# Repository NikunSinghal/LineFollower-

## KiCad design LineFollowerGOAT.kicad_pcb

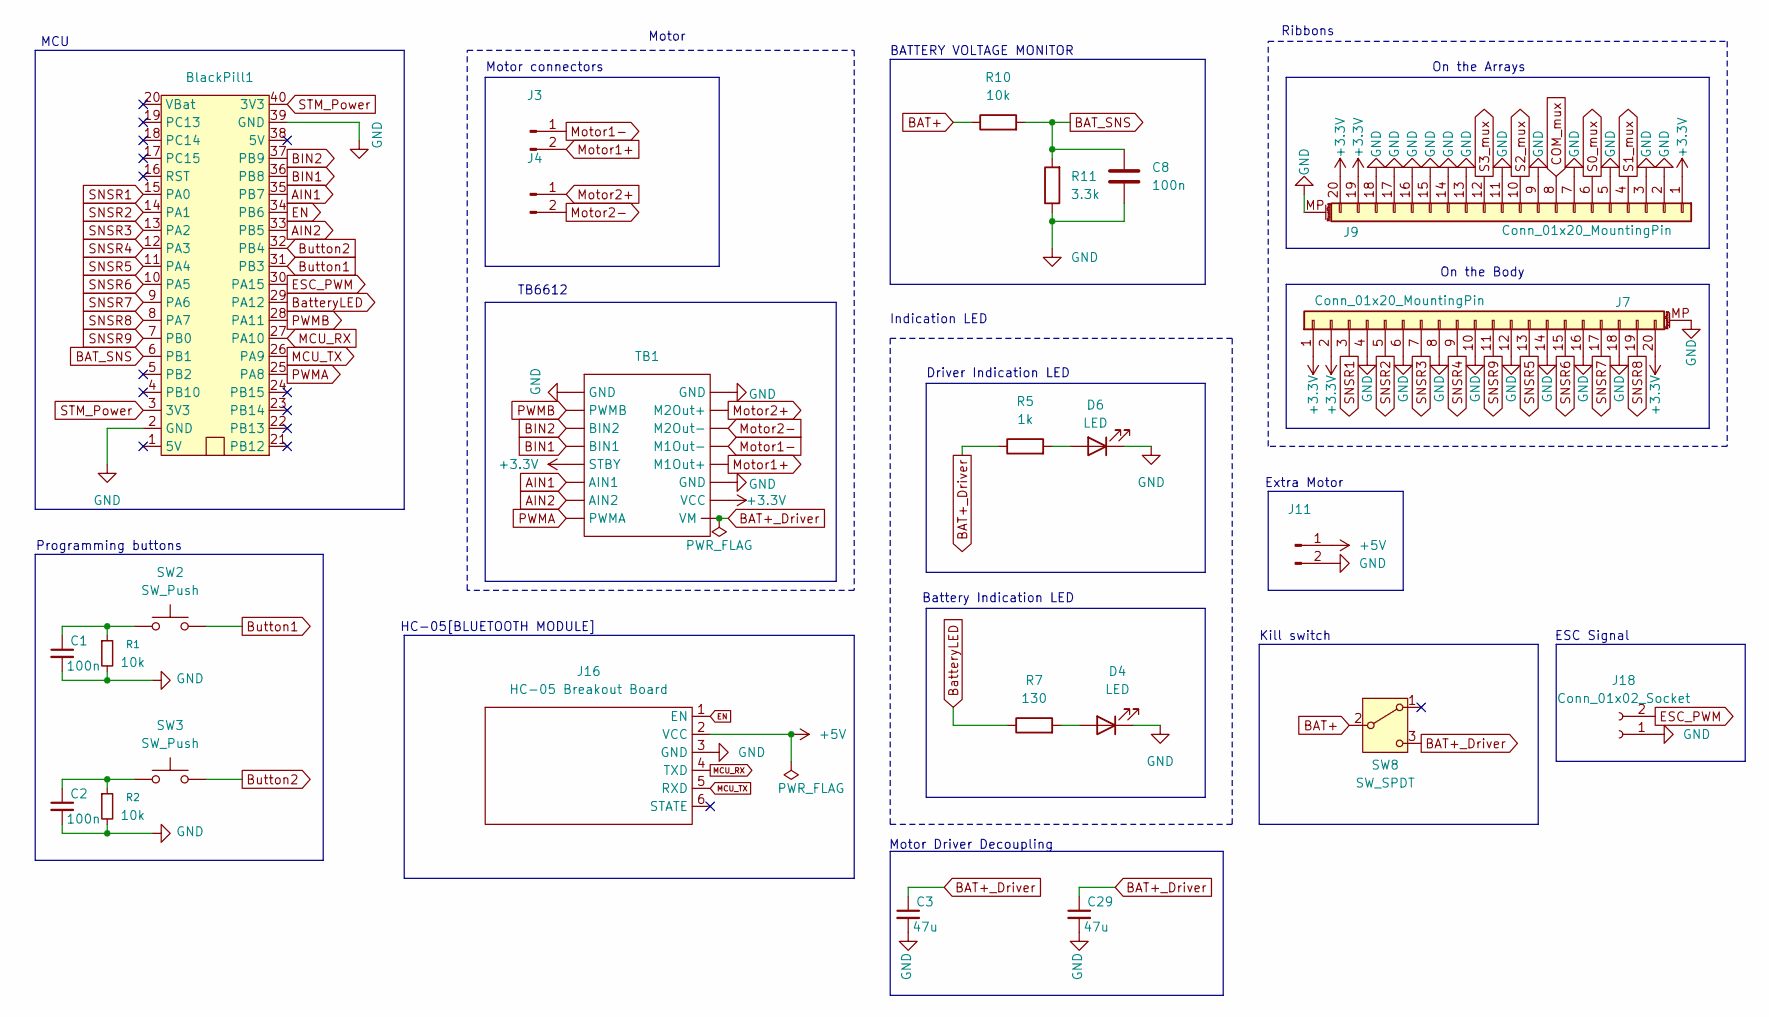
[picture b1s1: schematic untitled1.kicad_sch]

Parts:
BlackPill1: STM32F411_BP; blackpill_fp
C1, C2, C8: 100n; C_0603_1608Metric_Pad1.08x0.95mm_HandSolder
C3, C29: 47u; C_0603_1608Metric_Pad1.08x0.95mm_HandSolder
D4, D6: LED; LED_0603_1608Metric_Pad1.05x0.95mm_HandSolder
J3, J4: Conn_01x02_Pin; JST_PH_B2B-PH-K_1x02_P2.00mm_Vertical
J7, J9: Conn_01x20_MountingPin; Amphenol_F32Q-1A7x1-11020_1x20-1MP_P0.5mm_Horizontal
J11: Conn_01x02_Pin; PinHeader_1x02_P2.00mm_Vertical
J16: HC-05 Breakout Board; PinSocket_1x06_P2.54mm_Vertical
J18: Conn_01x02_Socket; JST_PH_B2B-PH-K_1x02_P2.00mm_Vertical
R1, R2, R10: 10k; R_0603_1608Metric_Pad0.98x0.95mm_HandSolder
R5: 1k; R_0603_1608Metric_Pad0.98x0.95mm_HandSolder
R7: 130; R_0603_1608Metric_Pad0.98x0.95mm_HandSolder
R11: 3.3k; R_0603_1608Metric_Pad0.98x0.95mm_HandSolder
SW2, SW3: SW_Push; Push button-fp
SW8: SW_SPDT; SW_Slide_SPDT_Angled_CK_OS102011MA1Q
TB1: TB6612 module

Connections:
+3.3V: J7.1, J7.2, J7.20, J9.1, J9.19, J9.20, TB1.5 (STBY), TB1.15 (VCC); also elsewhere on the board
+5V: J11.1, J16.2 (VCC); also elsewhere on the board
AIN1: BlackPill1.35 (PB7), TB1.6 (AIN1)
AIN2: BlackPill1.33 (PB5), TB1.7 (AIN2)
BAT+: R10.1, SW8.2 (B); also elsewhere on the board
BAT+_Driver: C3.1, C29.1, R5.1, SW8.3 (C), TB1.16 (VM)
BAT_SNS: BlackPill1.6 (PB1), C8.1, R10.2, R11.2
BIN1: BlackPill1.36 (PB8), TB1.4 (BIN1)
BIN2: BlackPill1.37 (PB9), TB1.3 (BIN2)
BatteryLED: BlackPill1.29 (PA12), R7.1
Button1: BlackPill1.31 (PB3), SW2.2
Button2: BlackPill1.32 (PB4), SW3.2
COM_mux: J9.8; also elsewhere on the board
EN: BlackPill1.34 (PB6), J16.1 (EN)
ESC_PWM: BlackPill1.30 (PA15), J18.2
GND: BlackPill1.2 (GND), BlackPill1.39 (GND), C1.2, C2.2, C3.2, C8.2, C29.2, D4.1 (K), D6.1 (K), J7.4, J7.6, J7.8, J7.10, J7.12, J7.14, J7.16, J7.18, J7.MP (MountPin), J9.2, J9.3, J9.5, J9.7, J9.9, J9.11, J9.13, J9.14, J9.15, J9.16, J9.17, J9.18, J9.MP (MountPin), J11.2, J16.3 (GND), J18.1, R1.2, R2.2, R11.1, TB1.1 (GND), TB1.9 (GND), TB1.14 (GND); also elsewhere on the board
MCU_RX: BlackPill1.27 (PA10), J16.4 (TXD)
MCU_TX: BlackPill1.26 (PA9), J16.5 (RXD)
Motor1+: J3.2, TB1.13 (M1Out+)
Motor1-: J3.1, TB1.12 (M1Out-)
Motor2+: J4.1, TB1.10 (M2Out+)
Motor2-: J4.2, TB1.11 (M2Out-)
unnamed: C1.1, R1.1, SW2.1
unnamed: C2.1, R2.1, SW3.1
unnamed: D4.2 (A), R7.2
unnamed: D6.2 (A), R5.2
PWMA: BlackPill1.25 (PA8), TB1.8 (PWMA)
PWMB: BlackPill1.28 (PA11), TB1.2 (PWMB)
S0_mux: J9.6; also elsewhere on the board
S1_mux: J9.4; also elsewhere on the board
S2_mux: J9.10; also elsewhere on the board
S3_mux: J9.12; also elsewhere on the board
SNSR1: BlackPill1.15 (PA0), J7.3
SNSR2: BlackPill1.14 (PA1), J7.5
SNSR3: BlackPill1.13 (PA2), J7.7
SNSR4: BlackPill1.12 (PA3), J7.9
SNSR5: BlackPill1.11 (PA4), J7.13
SNSR6: BlackPill1.10 (PA5), J7.15
SNSR7: BlackPill1.9 (PA6), J7.17
SNSR8: BlackPill1.8 (PA7), J7.19
SNSR9: BlackPill1.7 (PB0), J7.11
STM_Power: BlackPill1.3 (3V3), BlackPill1.40 (3V3); also elsewhere on the board

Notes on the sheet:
On the Body
Motor Driver Decoupling
Driver Indication LED
TB6612
Battery Indication LED
HC-05[BLUETOOTH MODULE]
Motor
BATTERY VOLTAGE MONITOR
ESC Signal
Motor connectors
MCU
Indication LED
Ribbons
On the Arrays
Kill switch
Programming buttons
Extra Motor

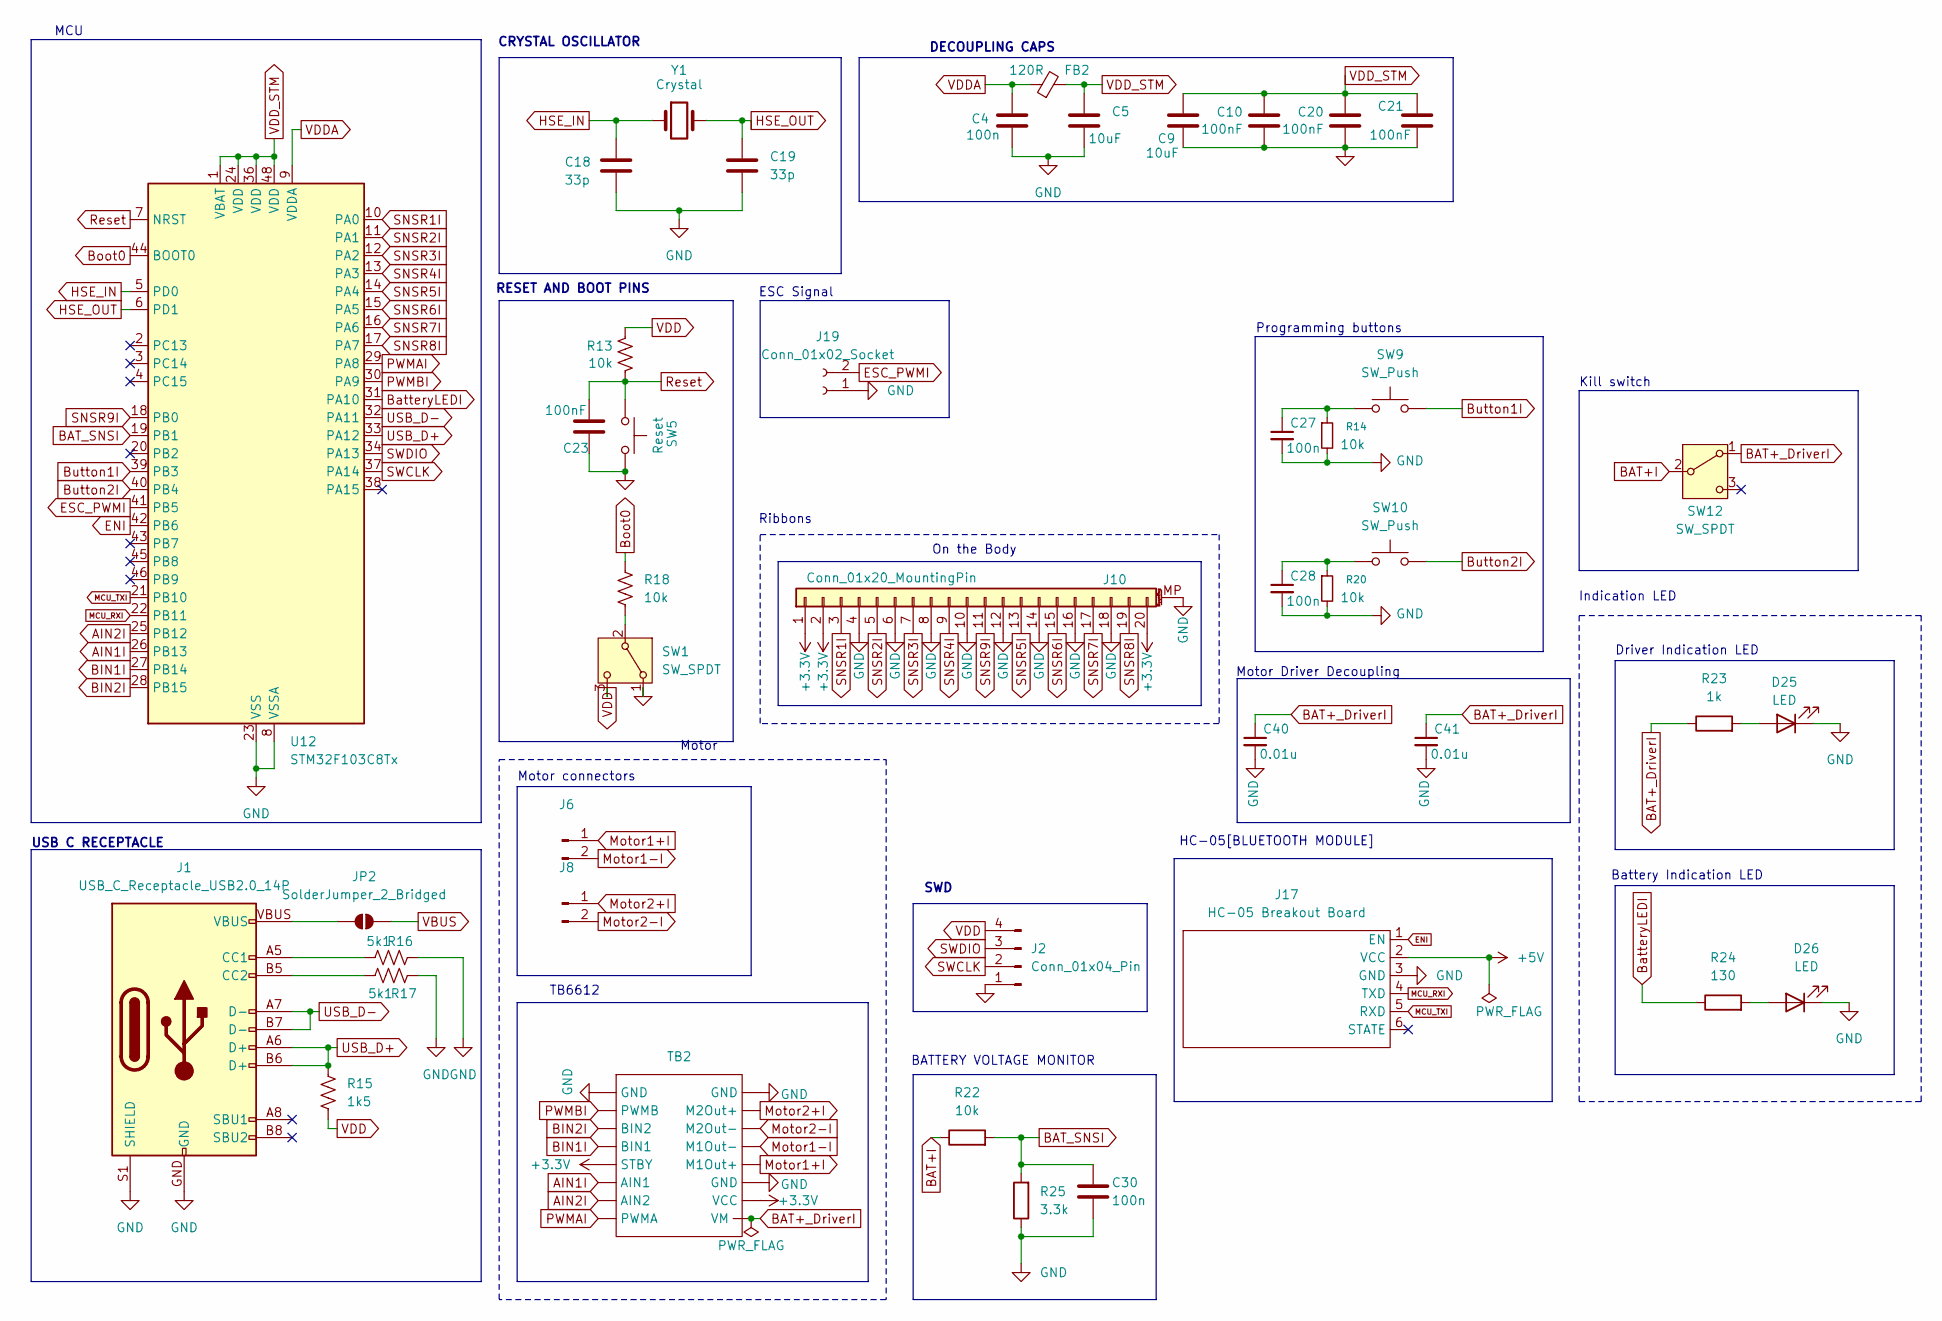
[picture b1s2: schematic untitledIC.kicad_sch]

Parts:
C4, C27, C28, C30: 100n; C_0603_1608Metric_Pad1.08x0.95mm_HandSolder
C5, C9: 10uF; C_0603_1608Metric_Pad1.08x0.95mm_HandSolder
C10, C20, C21, C23: 100nF; C_0603_1608Metric_Pad1.08x0.95mm_HandSolder
C18, C19: 33p; C_0603_1608Metric_Pad1.08x0.95mm_HandSolder
C40, C41: 0.01u; C_0603_1608Metric_Pad1.08x0.95mm_HandSolder
D25, D26: LED; LED_0603_1608Metric_Pad1.05x0.95mm_HandSolder
FB2: 120R; L_0603_1608Metric_Pad1.05x0.95mm_HandSolder
J1: USB_C_Receptacle_USB2.0_14P; USB-C-16P
J2: Conn_01x04_Pin; PinHeader_1x04_P2.00mm_Vertical
J6, J8: Conn_01x02_Pin; JST_PH_B2B-PH-K_1x02_P2.00mm_Vertical
J10: Conn_01x20_MountingPin; Amphenol_F32Q-1A7x1-11020_1x20-1MP_P0.5mm_Horizontal
J17: HC-05 Breakout Board; PinSocket_1x06_P2.54mm_Vertical
J19: Conn_01x02_Socket; JST_PH_B2B-PH-K_1x02_P2.00mm_Vertical
JP2: SolderJumper_2_Bridged; SolderJumper-2_P1.3mm_Open_RoundedPad1.0x1.5mm
R13, R14, R18, R20, R22: 10k; R_0603_1608Metric_Pad0.98x0.95mm_HandSolder
R15: 1k5; R_0603_1608Metric_Pad0.98x0.95mm_HandSolder
R16, R17: 5k1; R_0603_1608Metric_Pad0.98x0.95mm_HandSolder
R23: 1k; R_0603_1608Metric_Pad0.98x0.95mm_HandSolder
R24: 130; R_0603_1608Metric_Pad0.98x0.95mm_HandSolder
R25: 3.3k; R_0603_1608Metric_Pad0.98x0.95mm_HandSolder
SW1: SW_SPDT; PinHeader_1x03_P2.00mm_Vertical
SW5: Reset; Push button-fp
SW9, SW10: SW_Push; Push button-fp
SW12: SW_SPDT; SW_Slide_SPDT_Angled_CK_OS102011MA1Q
TB2: TB6612 module
U12: STM32F103C8Tx; LQFP-48_7x7mm_P0.5mm
Y1: Crystal; Crystal_SMD_HC49-SD

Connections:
+3.3V: J10.1, J10.2, J10.20, TB2.5 (STBY), TB2.15 (VCC); also elsewhere on the board
+5V: J17.2 (VCC); also elsewhere on the board
AIN1I: TB2.6 (AIN1), U12.26 (PB13)
AIN2I: TB2.7 (AIN2), U12.25 (PB12)
BAT+I: R22.1, SW12.2 (B); also elsewhere on the board
BAT+_DriverI: C40.1, C41.1, R23.1, SW12.1 (A), TB2.16 (VM)
BAT_SNSI: C30.1, R22.2, R25.2, U12.19 (PB1)
BIN1I: TB2.4 (BIN1), U12.27 (PB14)
BIN2I: TB2.3 (BIN2), U12.28 (PB15)
BatteryLEDI: R24.1, U12.31 (PA10)
Boot0: R18.2, U12.44 (BOOT0)
Button1I: SW9.2, U12.39 (PB3)
Button2I: SW10.2, U12.40 (PB4)
ENI: J17.1 (EN), U12.42 (PB6)
ESC_PWMI: J19.2, U12.41 (PB5)
GND: C4.2, C5.2, C9.2, C10.2, C18.2, C19.2, C20.2, C21.2, C23.1, C27.2, C28.2, C30.2, C40.2, C41.2, D25.1 (K), D26.1 (K), J1.A12 (GND), J1.B1 (GND), J1.B12 (GND), J1.GND, J1.S1 (SHIELD), J2.1, J10.4, J10.6, J10.8, J10.10, J10.12, J10.14, J10.16, J10.18, J10.MP (MountPin), J17.3 (GND), J19.1, R14.2, R16.2, R17.2, R20.2, R25.1, SW1.1 (A), SW5.2, TB2.1 (GND), TB2.9 (GND), TB2.14 (GND), U12.8 (VSSA), U12.23 (VSS), U12.35 (VSS), U12.47 (VSS); also elsewhere on the board
HSE_IN: C18.1, U12.5 (PD0), Y1.1
HSE_OUT: C19.1, U12.6 (PD1), Y1.2
MCU_RXI: J17.4 (TXD), U12.22 (PB11)
MCU_TXI: J17.5 (RXD), U12.21 (PB10)
Motor1+I: J6.1, TB2.13 (M1Out+)
Motor1-I: J6.2, TB2.12 (M1Out-)
Motor2+I: J8.1, TB2.10 (M2Out+)
Motor2-I: J8.2, TB2.11 (M2Out-)
unnamed: C27.1, R14.1, SW9.1
unnamed: C28.1, R20.1, SW10.1
unnamed: D25.2 (A), R23.2
unnamed: D26.2 (A), R24.2
unnamed: J1.A5 (CC1), R16.1
unnamed: J1.B5 (CC2), R17.1
unnamed: J1.A9 (VBUS), J1.B4 (VBUS), J1.B9 (VBUS), J1.VBUS, JP2.1 (A)
unnamed: R18.1, SW1.2 (B)
PWMAI: TB2.8 (PWMA), U12.29 (PA8)
PWMBI: TB2.2 (PWMB), U12.30 (PA9)
Reset: C23.2, R13.1, SW5.1, U12.7 (NRST)
SNSR1I: J10.3, U12.10 (PA0)
SNSR2I: J10.5, U12.11 (PA1)
SNSR3I: J10.7, U12.12 (PA2)
SNSR4I: J10.9, U12.13 (PA3)
SNSR5I: J10.13, U12.14 (PA4)
SNSR6I: J10.15, U12.15 (PA5)
SNSR7I: J10.17, U12.16 (PA6)
SNSR8I: J10.19, U12.17 (PA7)
SNSR9I: J10.11, U12.18 (PB0)
SWCLK: J2.2, U12.37 (PA14)
SWDIO: J2.3, U12.34 (PA13)
USB_D+: J1.A6 (D+), J1.B6 (D+), R15.1, U12.33 (PA12)
USB_D-: J1.A7 (D-), J1.B7 (D-), U12.32 (PA11)
VBUS: JP2.2 (B); also elsewhere on the board
VDD: J2.4, R13.2, R15.2, SW1.3 (C); also elsewhere on the board
VDDA: C4.1, FB2.1, U12.9 (VDDA)
VDD_STM: C5.1, C9.1, C10.1, C20.1, C21.1, FB2.2, U12.1 (VBAT), U12.24 (VDD), U12.36 (VDD), U12.48 (VDD); also elsewhere on the board

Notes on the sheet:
Programming buttons
Indication LED
CRYSTAL OSCILLATOR
On the Body
Motor Driver Decoupling
MCU
BATTERY VOLTAGE MONITOR
DECOUPLING CAPS
Battery Indication LED
Kill switch
ESC Signal
USB C RECEPTACLE
HC-05[BLUETOOTH MODULE]
Motor
Driver Indication LED
SWD
RESET AND BOOT PINS
Motor connectors
TB6612
Ribbons

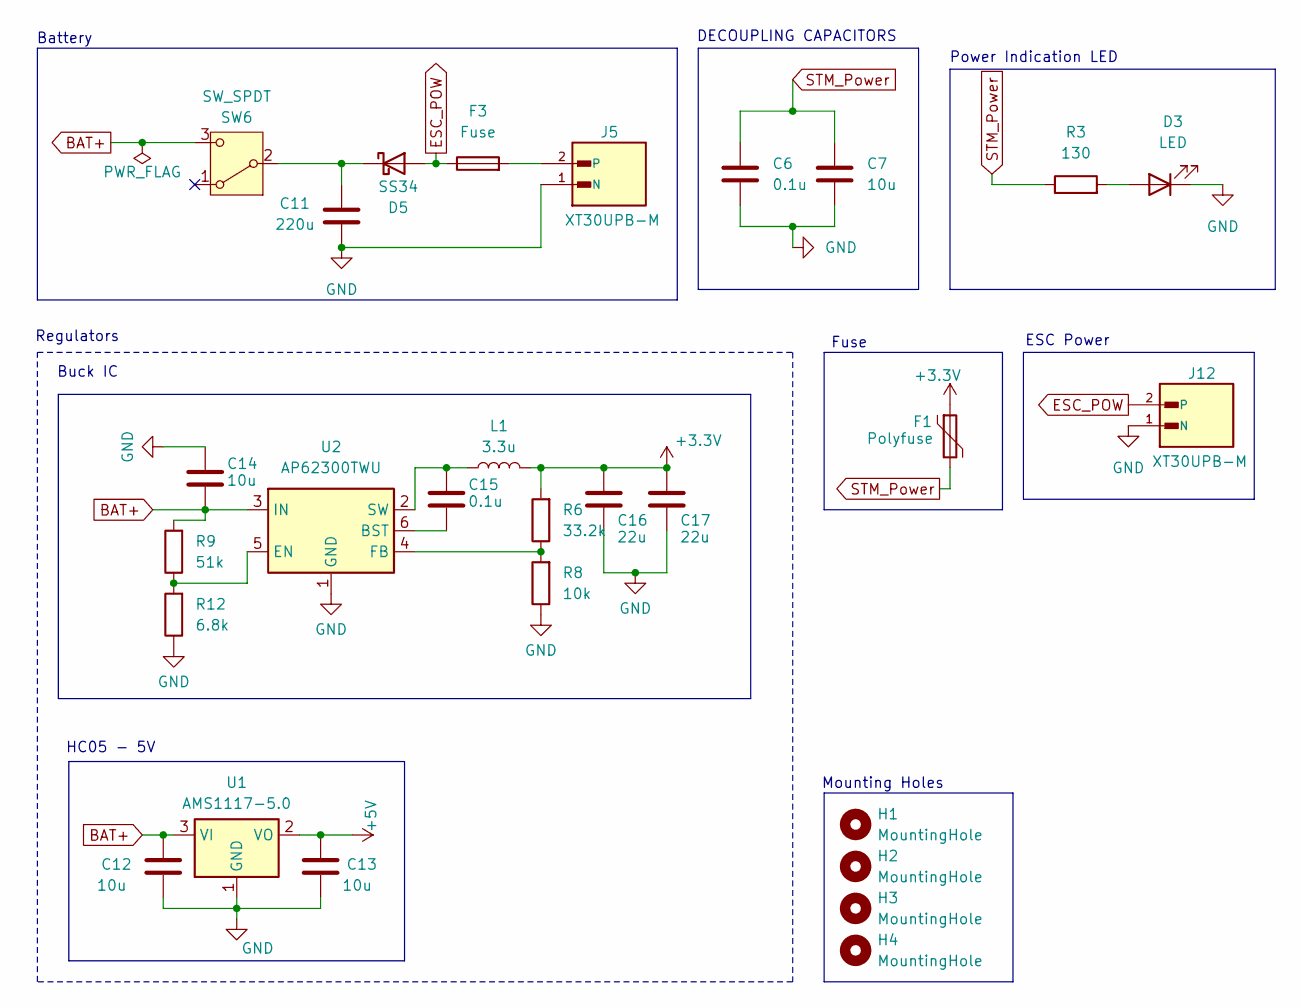
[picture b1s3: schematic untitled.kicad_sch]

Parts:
C6, C15: 0.1u; C_0603_1608Metric_Pad1.08x0.95mm_HandSolder
C7, C12, C13, C14: 10u; C_0603_1608Metric_Pad1.08x0.95mm_HandSolder
C11: 220u; CP_Radial_D6.3mm_P2.50mm
C16, C17: 22u; C_0603_1608Metric_Pad1.08x0.95mm_HandSolder
D3: LED; LED_0603_1608Metric_Pad1.05x0.95mm_HandSolder
D5: SS34; D_SMA_Handsoldering
F1: Polyfuse; Fuse_0805_2012Metric_Pad1.15x1.40mm_HandSolder
F3: Fuse; C_1808_4520Metric
H1, H2, H3, H4: MountingHole; MountingHole_3mm
J5, J12: XT30UPB-M; AMASS_XT30UPB-M_1x02_P5.0mm_Vertical
L1: 3.3u; L_Sunlord_SWPA5040S
R3: 130; R_0603_1608Metric_Pad0.98x0.95mm_HandSolder
R6: 33.2k; R_0603_1608Metric_Pad0.98x0.95mm_HandSolder
R8: 10k; R_0603_1608Metric_Pad0.98x0.95mm_HandSolder
R9: 51k; R_0603_1608Metric_Pad0.98x0.95mm_HandSolder
R12: 6.8k; R_0603_1608Metric_Pad0.98x0.95mm_HandSolder
SW6: SW_SPDT; SW_Slide_SPDT_Angled_CK_OS102011MA1Q
U1: AMS1117-5.0; SOT-223-3_TabPin2
U2: AP62300TWU; TSOT-23-6

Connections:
+3.3V: C16.1, C17.1, F1.1, L1.2, R6.2; also elsewhere on the board
+5V: C13.1, U1.2 (VO); also elsewhere on the board
BAT+: C12.1, C14.2, R9.2, SW6.3 (C), U1.3 (VI), U2.3 (IN); also elsewhere on the board
ESC_POW: D5.2 (A), F3.1, J12.2
GND: C6.2, C7.2, C11.2, C12.2, C13.2, C14.1, C16.2, C17.2, D3.1 (K), J5.1 (N), J12.1 (N), R8.1, R12.1, U1.1 (GND), U2.1 (GND); also elsewhere on the board
unnamed: D3.2 (A), R3.2
unnamed: C11.1, D5.1 (K), SW6.2 (B)
unnamed: F3.2, J5.2
unnamed: C15.2, U2.6 (BST)
unnamed: R9.1, R12.2, U2.5 (EN)
unnamed: R6.1, R8.2, U2.4 (FB)
unnamed: C15.1, L1.1, U2.2 (SW)
STM_Power: C6.1, C7.1, F1.2, R3.1; also elsewhere on the board

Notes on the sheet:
Regulators
DECOUPLING CAPACITORS
Power Indication LED
ESC Power
Fuse
Battery
Buck IC
Mounting Holes
HC05 - 5V

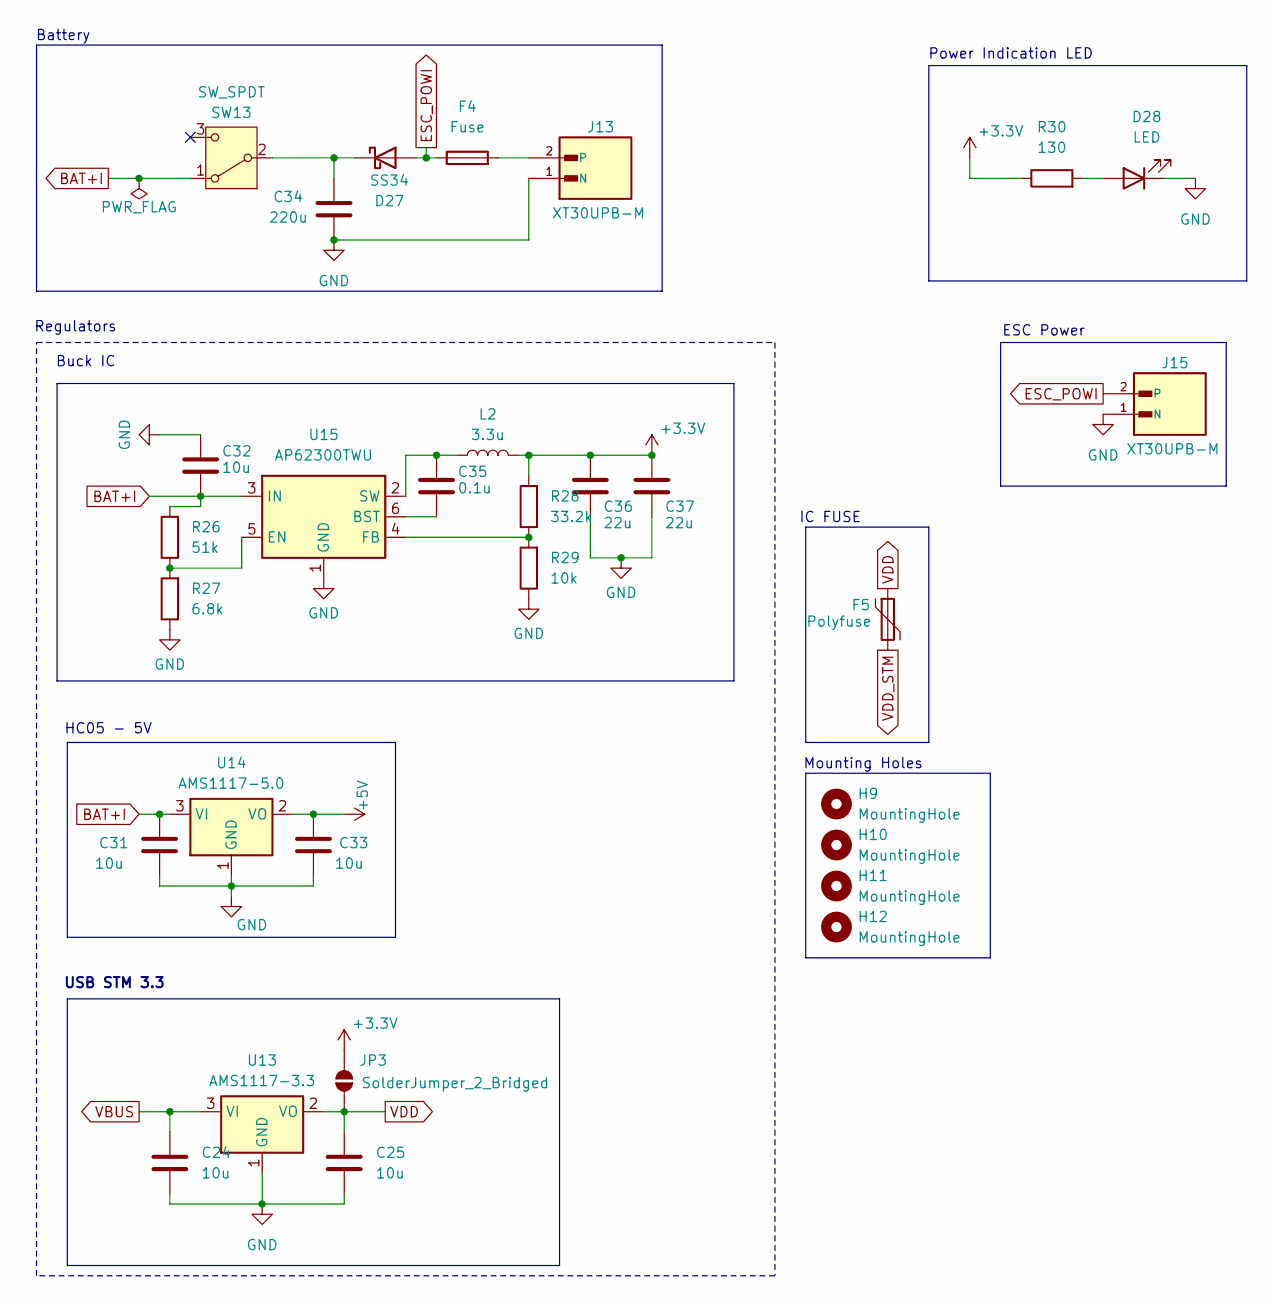
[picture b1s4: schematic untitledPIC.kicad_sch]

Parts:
C24, C25, C31, C32, C33: 10u; C_0603_1608Metric_Pad1.08x0.95mm_HandSolder
C34: 220u; CP_Radial_D6.3mm_P2.50mm
C35: 0.1u; C_0603_1608Metric_Pad1.08x0.95mm_HandSolder
C36, C37: 22u; C_0603_1608Metric_Pad1.08x0.95mm_HandSolder
D27: SS34; D_SMA_Handsoldering
D28: LED; LED_0603_1608Metric_Pad1.05x0.95mm_HandSolder
F4: Fuse; C_1808_4520Metric
F5: Polyfuse; Fuse_0805_2012Metric_Pad1.15x1.40mm_HandSolder
H9, H10, H11, H12: MountingHole; MountingHole_3mm
J13, J15: XT30UPB-M; AMASS_XT30UPB-M_1x02_P5.0mm_Vertical
JP3: SolderJumper_2_Bridged; SolderJumper-2_P1.3mm_Open_RoundedPad1.0x1.5mm
L2: 3.3u; L_Sunlord_SWPA5040S
R26: 51k; R_0603_1608Metric_Pad0.98x0.95mm_HandSolder
R27: 6.8k; R_0603_1608Metric_Pad0.98x0.95mm_HandSolder
R28: 33.2k; R_0603_1608Metric_Pad0.98x0.95mm_HandSolder
R29: 10k; R_0603_1608Metric_Pad0.98x0.95mm_HandSolder
R30: 130; R_0603_1608Metric_Pad0.98x0.95mm_HandSolder
SW13: SW_SPDT; SW_Slide_SPDT_Angled_CK_OS102011MA1Q
U13: AMS1117-3.3; SOT-223-3_TabPin2
U14: AMS1117-5.0; SOT-223-3_TabPin2
U15: AP62300TWU; TSOT-23-6

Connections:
+3.3V: C36.1, C37.1, JP3.2 (B), L2.2, R28.2, R30.1; also elsewhere on the board
+5V: C33.1, U14.2 (VO); also elsewhere on the board
BAT+I: C31.1, C32.2, R26.2, SW13.1 (A), U14.3 (VI), U15.3 (IN); also elsewhere on the board
ESC_POWI: D27.2 (A), F4.1, J15.2
GND: C24.2, C25.2, C31.2, C32.1, C33.2, C34.2, C36.2, C37.2, D28.1 (K), J13.1 (N), J15.1 (N), R27.1, R29.1, U13.1 (GND), U14.1 (GND), U15.1 (GND); also elsewhere on the board
unnamed: C34.1, D27.1 (K), SW13.2 (B)
unnamed: D28.2 (A), R30.2
unnamed: F4.2, J13.2
unnamed: C35.2, U15.6 (BST)
unnamed: R26.1, R27.2, U15.5 (EN)
unnamed: R28.1, R29.2, U15.4 (FB)
unnamed: C35.1, L2.1, U15.2 (SW)
VBUS: C24.1, U13.3 (VI); also elsewhere on the board
VDD: C25.1, F5.1, JP3.1 (A), U13.2 (VO); also elsewhere on the board
VDD_STM: F5.2; also elsewhere on the board

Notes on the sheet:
USB STM 3.3
Battery
ESC Power
Power Indication LED
HC05 - 5V
Buck IC
Mounting Holes
IC FUSE
Regulators

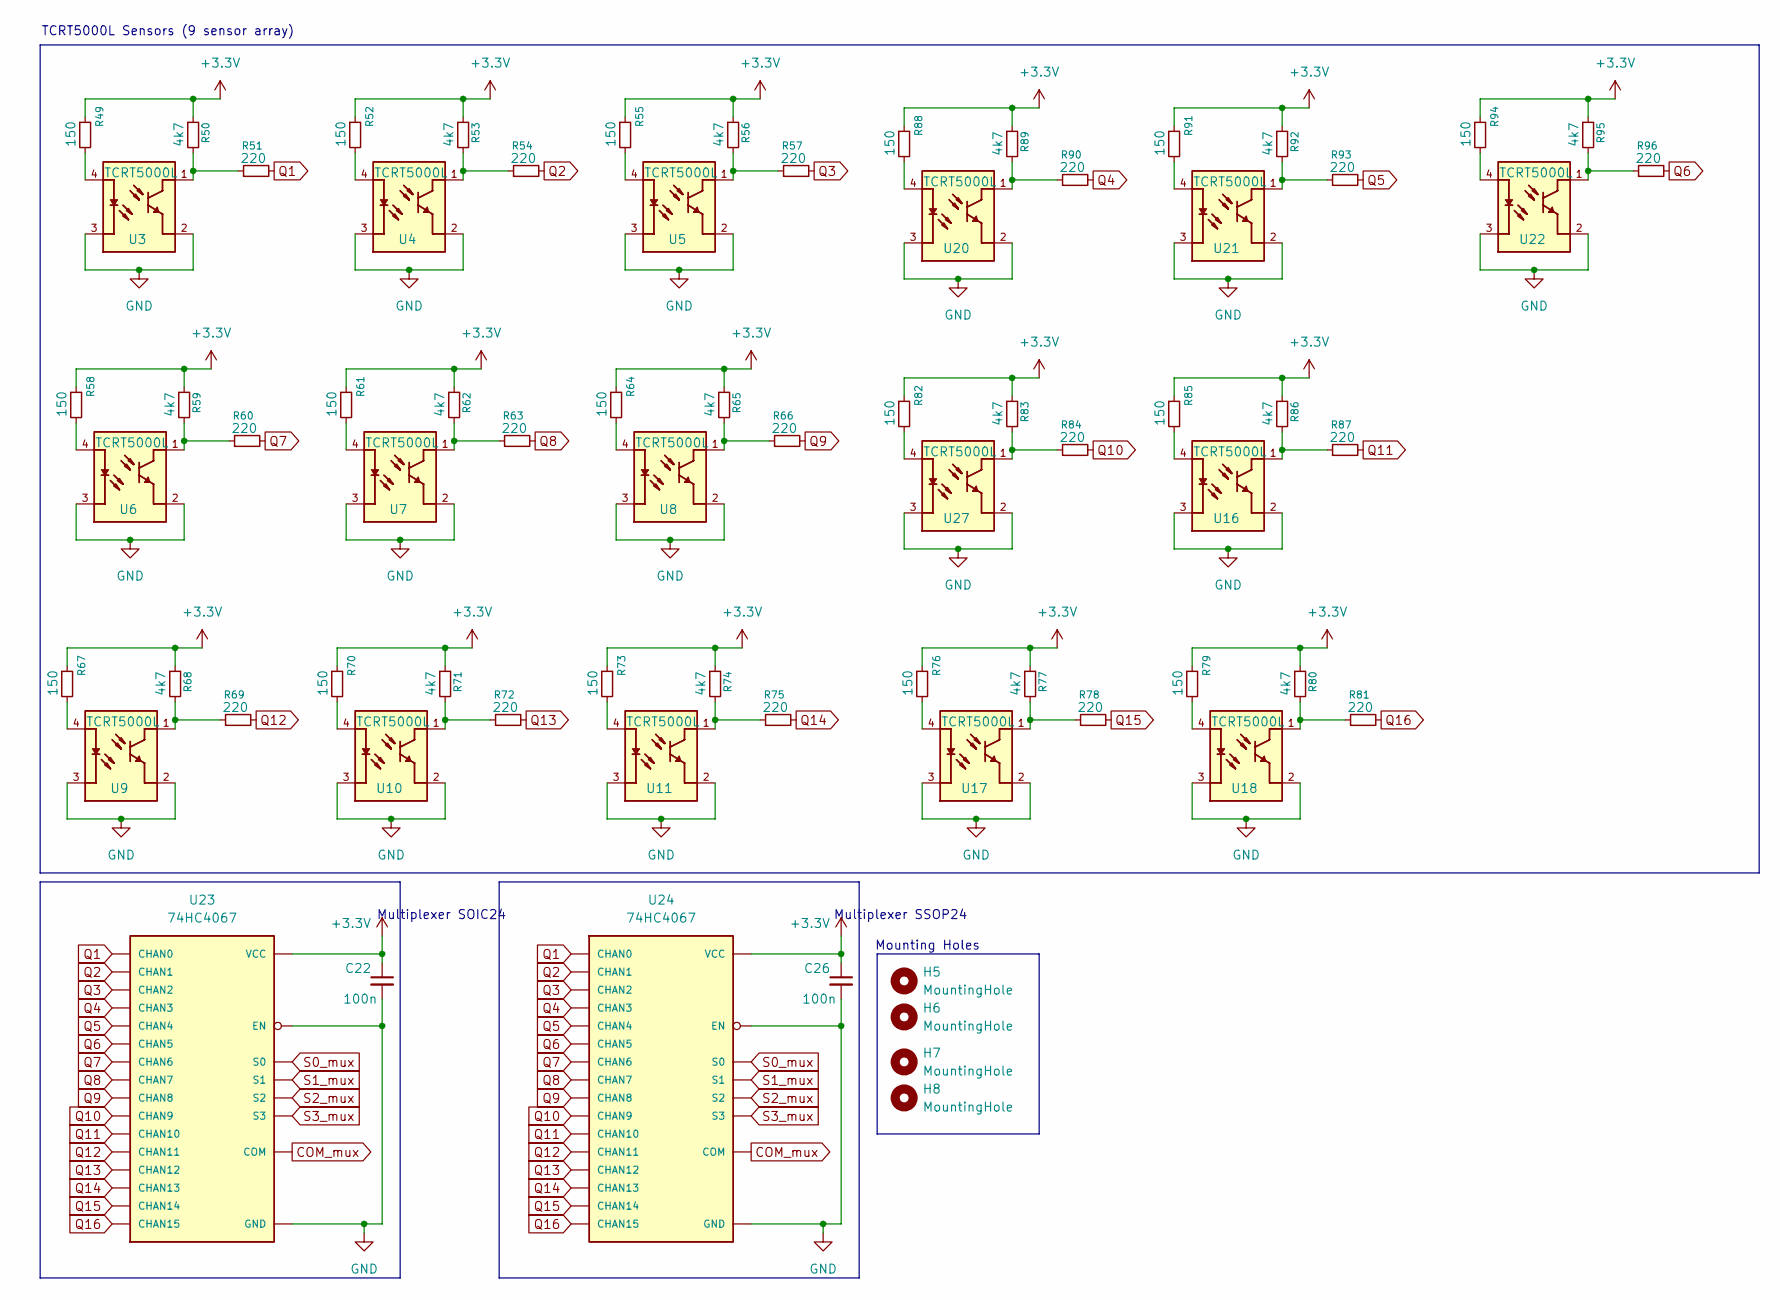
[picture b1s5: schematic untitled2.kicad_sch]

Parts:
C22, C26: 100n; C_0603_1608Metric_Pad1.08x0.95mm_HandSolder
H5, H6, H7, H8: MountingHole; MountingHole_3mm
R49, R52, R55, R58, R61, R64, R67, R70, R73, R76, R79, R82, R85, R88, R91, R94: 150; R_0603_1608Metric_Pad0.98x0.95mm_HandSolder
R50, R53, R56, R59, R62, R65, R68, R71, R74, R77, R80, R83, R86, R89, R92, R95: 4k7; R_0603_1608Metric_Pad0.98x0.95mm_HandSolder
R51, R54, R57, R60, R63, R66, R69, R72, R75, R78, R81, R84, R87, R90, R93, R96: 220; R_0603_1608Metric_Pad0.98x0.95mm_HandSolder
U3, U4, U5, U6, U7, U8, U9, U10, U11, U16, U17, U18, U20, U21, U22, U27: TCRT5000L; XDCR_TCRT5000L
U23: 74HC4067; SOIC-24W_7.5x15.4mm_P1.27mm
U24: 74HC4067; TSSOP-24_4.4x7.8mm_P0.65mm

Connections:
+3.3V: C22.1, C26.1, R49.1, R50.1, R52.1, R53.1, R55.1, R56.1, R58.1, R59.1, R61.1, R62.1, R64.1, R65.1, R67.1, R68.1, R70.1, R71.1, R73.1, R74.1, R76.1, R77.1, R79.1, R80.1, R82.1, R83.1, R85.1, R86.1, R88.1, R89.1, R91.1, R92.1, R94.1, R95.1, U23.24 (VCC), U24.24 (VCC); also elsewhere on the board
COM_mux: U23.1 (COM), U24.1 (COM); also elsewhere on the board
GND: C22.2, C26.2, U3.2, U3.3, U4.2, U4.3, U5.2, U5.3, U6.2, U6.3, U7.2, U7.3, U8.2, U8.3, U9.2, U9.3, U10.2, U10.3, U11.2, U11.3, U16.2, U16.3, U17.2, U17.3, U18.2, U18.3, U20.2, U20.3, U21.2, U21.3, U22.2, U22.3, U23.12 (GND), U23.15 (EN), U24.12 (GND), U24.15 (EN), U27.2, U27.3; also elsewhere on the board
unnamed: R49.2, U3.4
unnamed: R50.2, R51.1, U3.1
unnamed: R52.2, U4.4
unnamed: R53.2, R54.1, U4.1
unnamed: R55.2, U5.4
unnamed: R56.2, R57.1, U5.1
unnamed: R58.2, U6.4
unnamed: R59.2, R60.1, U6.1
unnamed: R61.2, U7.4
unnamed: R62.2, R63.1, U7.1
unnamed: R64.2, U8.4
unnamed: R65.2, R66.1, U8.1
unnamed: R67.2, U9.4
unnamed: R68.2, R69.1, U9.1
unnamed: R70.2, U10.4
unnamed: R71.2, R72.1, U10.1
unnamed: R73.2, U11.4
unnamed: R74.2, R75.1, U11.1
unnamed: R76.2, U17.4
unnamed: R77.2, R78.1, U17.1
unnamed: R79.2, U18.4
unnamed: R80.2, R81.1, U18.1
unnamed: R82.2, U27.4
unnamed: R83.2, R84.1, U27.1
unnamed: R85.2, U16.4
unnamed: R86.2, R87.1, U16.1
unnamed: R88.2, U20.4
unnamed: R89.2, R90.1, U20.1
unnamed: R91.2, U21.4
unnamed: R92.2, R93.1, U21.1
unnamed: R94.2, U22.4
unnamed: R95.2, R96.1, U22.1
Q1: R51.2, U23.9 (CHAN0), U24.9 (CHAN0)
Q2: R54.2, U23.8 (CHAN1), U24.8 (CHAN1)
Q3: R57.2, U23.7 (CHAN2), U24.7 (CHAN2)
Q4: R90.2, U23.6 (CHAN3), U24.6 (CHAN3)
Q5: R93.2, U23.5 (CHAN4), U24.5 (CHAN4)
Q6: R96.2, U23.4 (CHAN5), U24.4 (CHAN5)
Q7: R60.2, U23.3 (CHAN6), U24.3 (CHAN6)
Q8: R63.2, U23.2 (CHAN7), U24.2 (CHAN7)
Q9: R66.2, U23.23 (CHAN8), U24.23 (CHAN8)
Q10: R84.2, U23.22 (CHAN9), U24.22 (CHAN9)
Q11: R87.2, U23.21 (CHAN10), U24.21 (CHAN10)
Q12: R69.2, U23.20 (CHAN11), U24.20 (CHAN11)
Q13: R72.2, U23.19 (CHAN12), U24.19 (CHAN12)
Q14: R75.2, U23.18 (CHAN13), U24.18 (CHAN13)
Q15: R78.2, U23.17 (CHAN14), U24.17 (CHAN14)
Q16: R81.2, U23.16 (CHAN15), U24.16 (CHAN15)
S0_mux: U23.10 (S0), U24.10 (S0); also elsewhere on the board
S1_mux: U23.11 (S1), U24.11 (S1); also elsewhere on the board
S2_mux: U23.14 (S2), U24.14 (S2); also elsewhere on the board
S3_mux: U23.13 (S3), U24.13 (S3); also elsewhere on the board

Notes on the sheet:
Multiplexer SSOP24
TCRT5000L Sensors (9 sensor array)
Multiplexer SOIC24
Mounting Holes

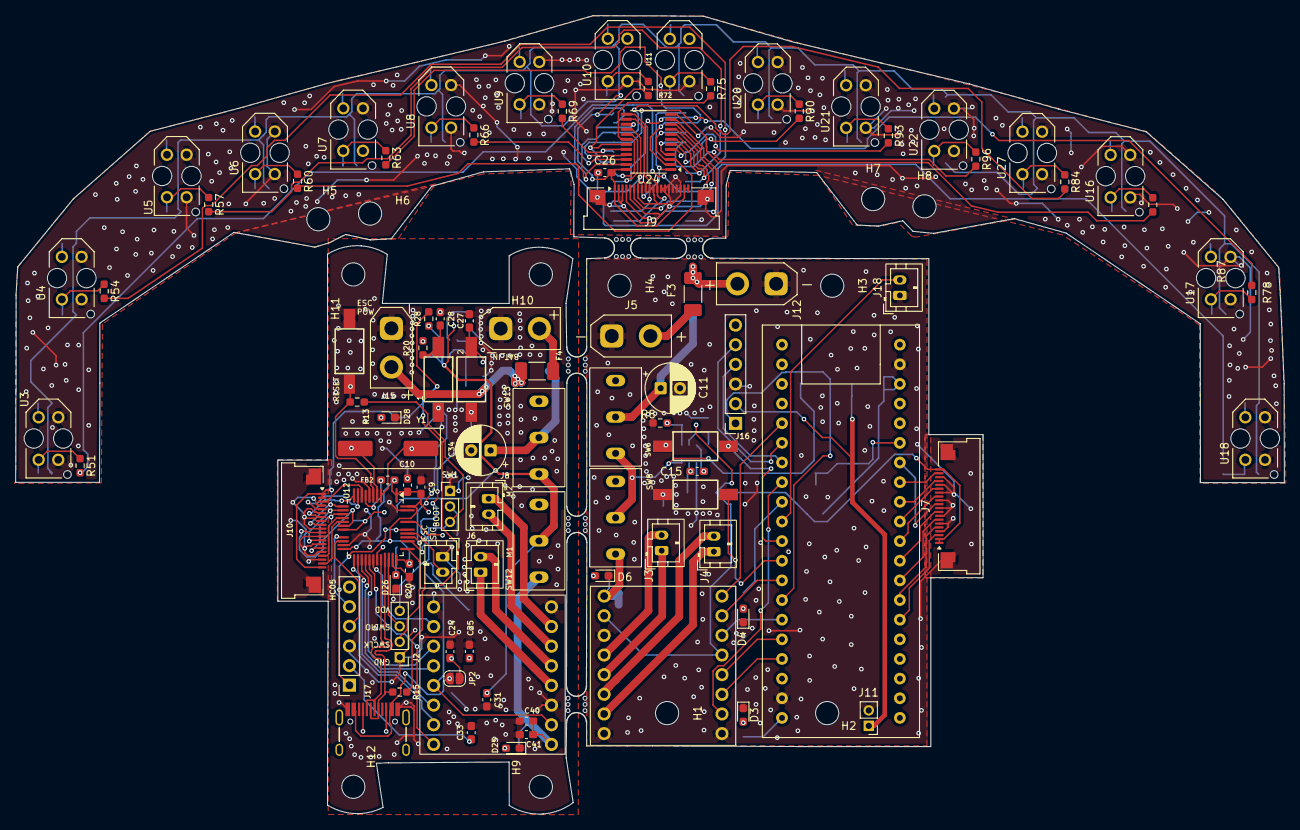
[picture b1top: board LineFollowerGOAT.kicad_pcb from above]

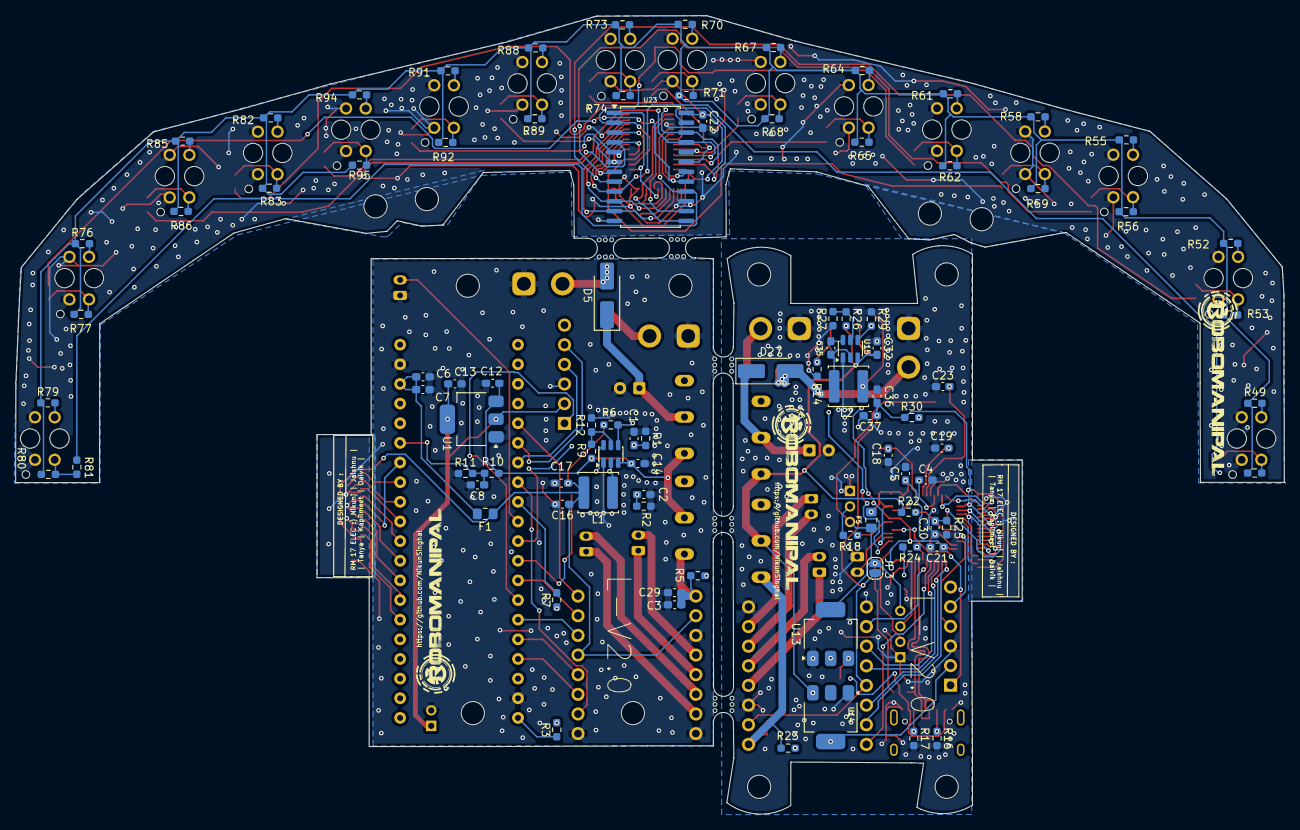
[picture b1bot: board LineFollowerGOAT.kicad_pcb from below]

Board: 2 copper layers, 164.0 x 103.2 mm, 204 parts (92 on the bottom side), 155 nets.

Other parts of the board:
mouse-bite-2.54mm-slot, mouse-bite-2.54mm-slot#2, mouse-bite-2.54mm-slot#3, mouse-bite-2.54mm-slot#4, mouse-bite-2.54mm-slot#5: VAL**; mouse-bite-2.54mm-slot
